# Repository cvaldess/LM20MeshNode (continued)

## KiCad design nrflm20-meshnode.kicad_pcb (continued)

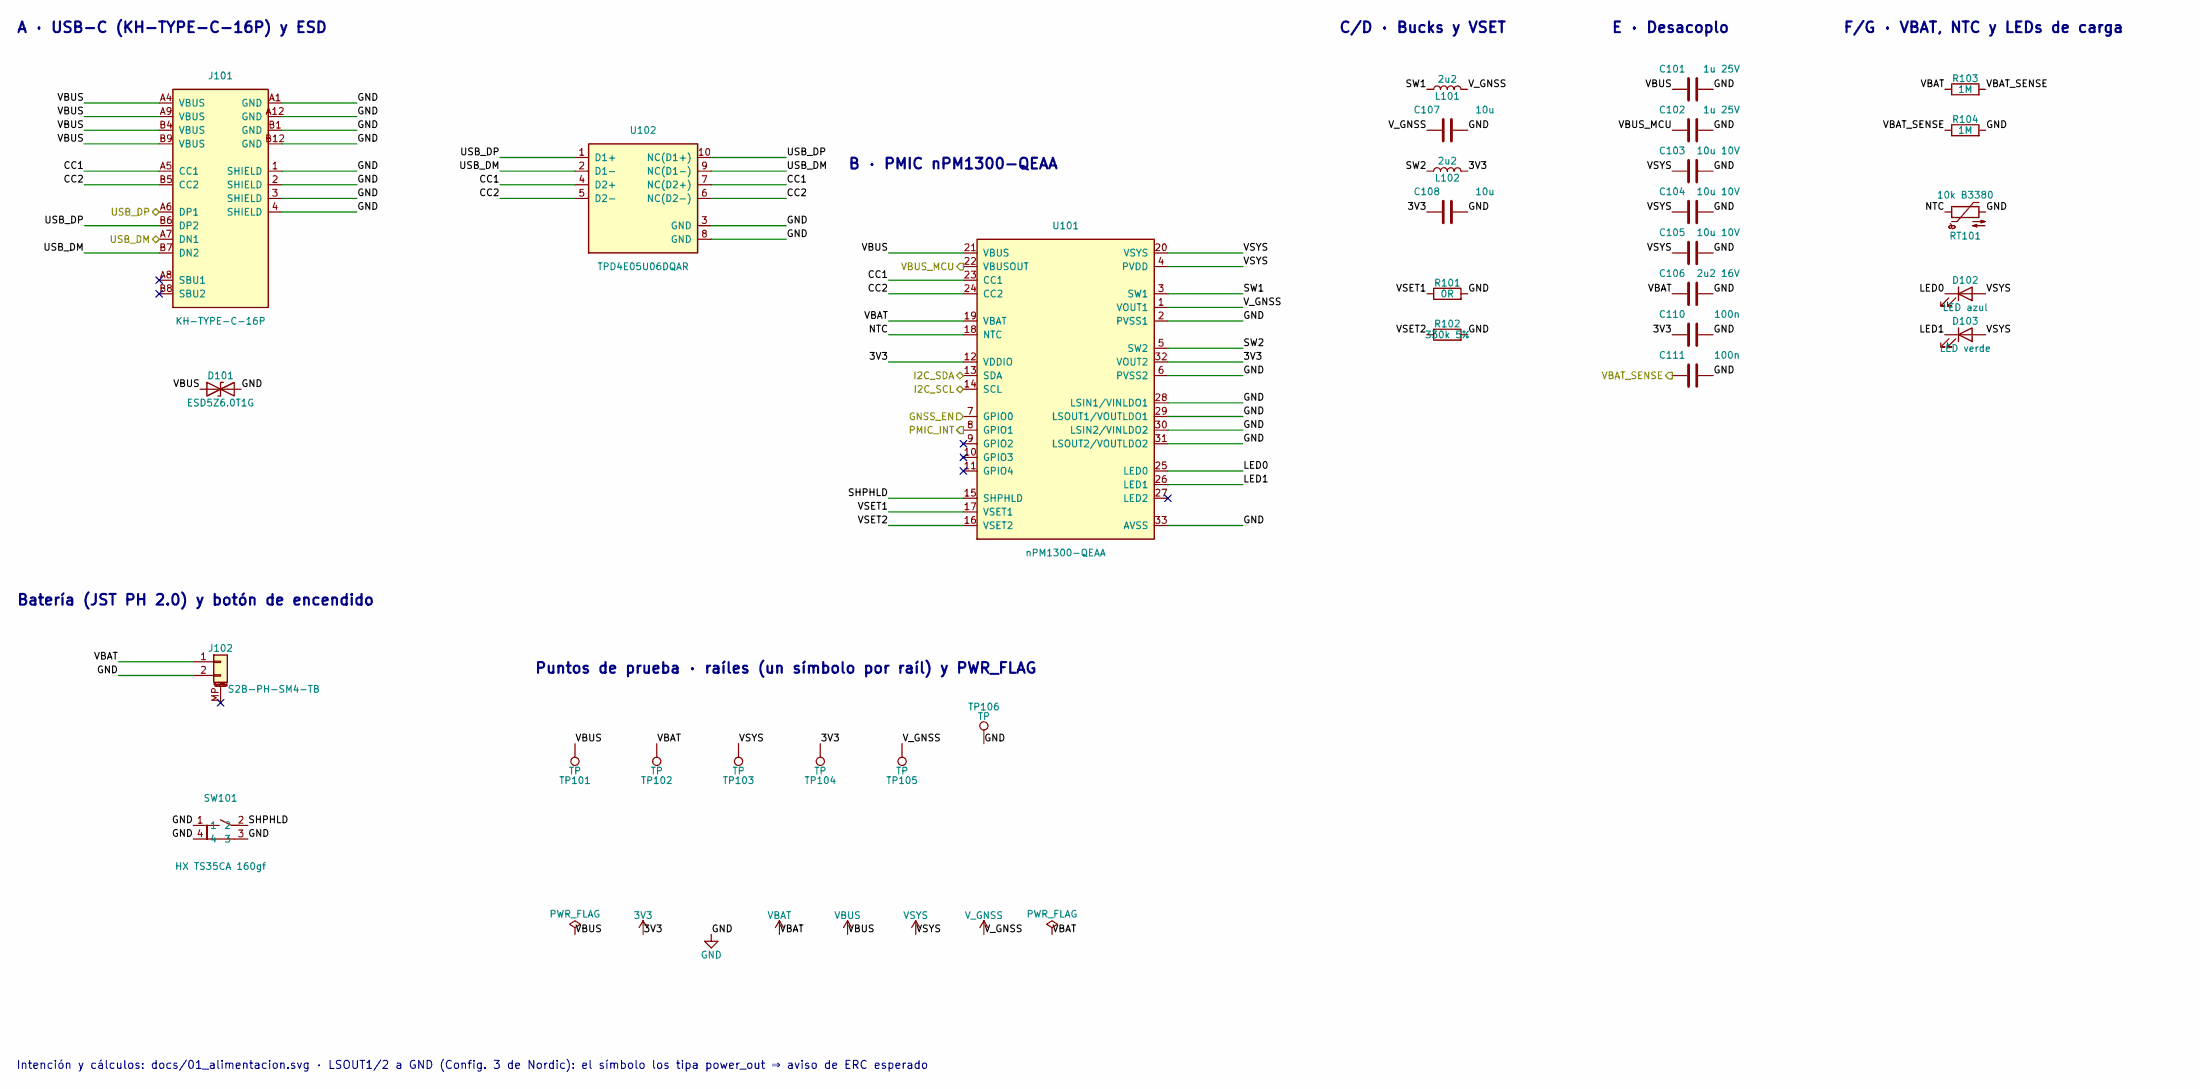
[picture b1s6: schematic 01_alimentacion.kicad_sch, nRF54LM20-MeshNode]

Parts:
C101, C102: 1u 25V; C_0402_1005Metric; MPN CL05A105KA5NQNC; LCSC Part C52923
C103, C104, C105: 10u 10V; C_0603_1608Metric
C106: 2u2 16V; C_0603_1608Metric; MPN CL10A225KO8NNNC; LCSC Part C23630
C107, C108: 10u; C_0603_1608Metric
C110, C111: 100n; C_0402_1005Metric; MPN CL05B104KO5NNNC; LCSC Part C1525
D101: ESD5Z6.0T1G; SOD-523F_L1.2-W0.8-LS1.7-RD; MPN ESD5Z6.0T1G; LCSC Part C82323
D102: LED azul; LED_0603_1608Metric; MPN XL-1608UBC-06A; LCSC Part C7371904
D103: LED verde; LED_0603_1608Metric; MPN XL-1608UGC-06A; LCSC Part C7371903
J101: KH-TYPE-C-16P; USB-C-SMD_KH-TYPE-C-16P; MPN KH-TYPE-C-16P; LCSC Part C709357
J102: S2B-PH-SM4-TB; JST_PH_S2B-PH-SM4-TB_1x02-1MP_P2.00mm_Horizontal; MPN S2B-PH-SM4-TB(LF)(SN); LCSC Part C295747
L101, L102: 2u2; L_Changjiang_FTC201610S; MPN APH201610C2R2MP01; LCSC Part C42455301
R101: 0R; R_0402_1005Metric; MPN RC0402FR-070RL; LCSC Part C106231
R102: 330k 5%; R_0402_1005Metric; MPN RC0402JR-07330KL; LCSC Part C137882
R103, R104: 1M; R_0402_1005Metric; MPN RC0402FR-071ML; LCSC Part C138033
RT101: 10k B3380; R_0402_1005Metric; MPN NCP15XH103F0SRC; LCSC Part C91636
SW101: HX TS35CA 160gf; KEY-SMD_HX-TS35CA-250GF; MPN HX TS35CA 160gf; LCSC Part C25168837
TP101, TP102, TP103, TP104, TP105, TP106: TP; TestPoint_Pad_D1.0mm
U101: nPM1300-QEAA; nPM1300-QFN32-EP3.5; MPN nPM1300-QEAA; LCSC Part C7501206
U102: TPD4E05U06DQAR; DFN2510-10_L2.5-W1.0-P0.50-BL; MPN TPD4E05U06DQAR; LCSC Part C22390021

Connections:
3V3: C108.1, C110.1, L102.2, TP104.1 (1_1), U101.12 (VDDIO), U101.32 (VOUT2); also elsewhere on the board
/01_alimentacion/CC1: J101.A5 (CC1), U101.23 (CC1), U102.4 (D2+), U102.7 (NC(D2+))
/01_alimentacion/CC2: J101.B5 (CC2), U101.24 (CC2), U102.5 (D2-), U102.6 (NC(D2-))
/01_alimentacion/LED0: D102.1 (K), U101.25 (LED0)
/01_alimentacion/LED1: D103.1 (K), U101.26 (LED1)
/01_alimentacion/NTC: RT101.1, U101.18 (NTC)
/01_alimentacion/SHPHLD: SW101.2, U101.15 (SHPHLD)
/01_alimentacion/SW1: L101.1, U101.3 (SW1)
/01_alimentacion/SW2: L102.1, U101.5 (SW2)
/01_alimentacion/VSET1: R101.1, U101.17 (VSET1)
/01_alimentacion/VSET2: R102.1, U101.16 (VSET2)
/GNSS_EN: U101.7 (GPIO0); also elsewhere on the board
/I2C_SCL: U101.14 (SCL); also elsewhere on the board
/I2C_SDA: U101.13 (SDA); also elsewhere on the board
/PMIC_INT: U101.8 (GPIO1); also elsewhere on the board
/USB_DM: J101.A7 (DN1), J101.B7 (DN2), U102.2 (D1-), U102.9 (NC(D1-)); also elsewhere on the board
/USB_DP: J101.A6 (DP1), J101.B6 (DP2), U102.1 (D1+), U102.10 (NC(D1+)); also elsewhere on the board
/VBAT_SENSE: C111.1, R103.2, R104.1; also elsewhere on the board
/VBUS_MCU: C102.1, U101.22 (VBUSOUT); also elsewhere on the board
GND: C101.2, C102.2, C103.2, C104.2, C105.2, C106.2, C107.2, C108.2, C110.2, C111.2, D101.2 (A2), J101.1 (SHIELD), J101.2 (SHIELD), J101.3 (SHIELD), J101.4 (SHIELD), J101.A1 (GND), J101.A12 (GND), J101.B1 (GND), J101.B12 (GND), J102.2, R101.2, R102.2, R104.2, RT101.2, SW101.1, SW101.3, SW101.4, TP106.1 (1_1), U101.2 (PVSS1), U101.6 (PVSS2), U101.28 (LSIN1/VINLDO1), U101.29 (LSOUT1/VOUTLDO1), U101.30 (LSIN2/VINLDO2), U101.31 (LSOUT2/VOUTLDO2), U101.33 (AVSS), U102.3 (GND), U102.8 (GND); also elsewhere on the board
VBAT: C106.1, J102.1, R103.1, TP102.1 (1_1), U101.19 (VBAT)
VBUS: C101.1, D101.1 (A1), J101.A4 (VBUS), J101.A9 (VBUS), J101.B4 (VBUS), J101.B9 (VBUS), TP101.1 (1_1), U101.21 (VBUS)
VSYS: C103.1, C104.1, C105.1, D102.2 (A), D103.2 (A), TP103.1 (1_1), U101.4 (PVDD), U101.20 (VSYS); also elsewhere on the board
V_GNSS: C107.1, L101.2, TP105.1 (1_1), U101.1 (VOUT1); also elsewhere on the board

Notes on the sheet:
B · PMIC nPM1300-QEAA
E · Desacoplo
F/G · VBAT, NTC y LEDs de carga
C/D · Bucks y VSET
Puntos de prueba · raíles (un símbolo por raíl) y PWR_FLAG
Batería (JST PH 2.0) y botón de encendido
A · USB-C (KH-TYPE-C-16P) y ESD
Intención y cálculos: docs/01_alimentacion.svg · LSOUT1/2 a GND (Config. 3 de Nordic): el símbolo los tipa power_out ⇒ aviso de ERC esperado

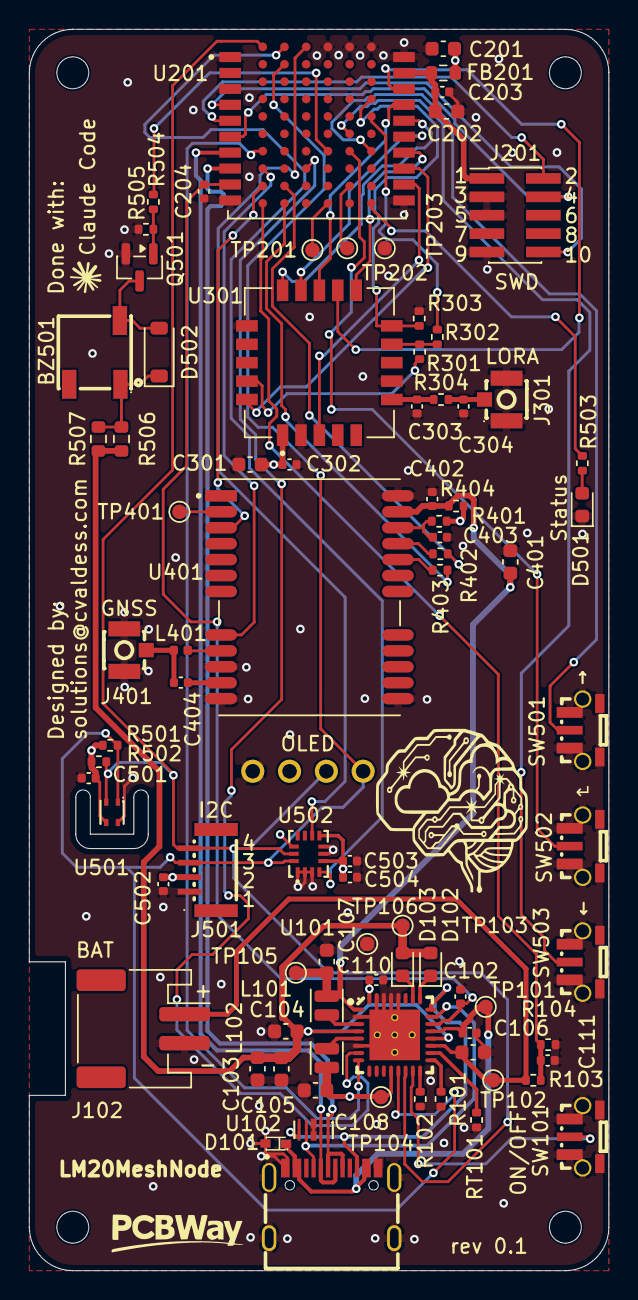
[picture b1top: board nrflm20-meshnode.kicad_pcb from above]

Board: 4 copper layers, 40.0 x 85.7 mm, 89 parts (1 on the bottom side), 65 nets.

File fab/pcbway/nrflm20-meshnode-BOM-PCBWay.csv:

"Designator","Qty","Manufacturer","Mfg Part #","Description/Value","Package/Footprint","LCSC Part #"
"BZ501","1","Huayu","HYG-5020A","HYG-5020A","easyeda2kicad:BUZ-SMD_3P-L5.0-W5.0-P3.50-BL","C7544810"
"C101,C102,C204,C502","4","Samsung","CL05A105KA5NQNC","1u 25V","Capacitor_SMD:C_0402_1005Metric","C52923"
"C103,C104,C105,C107,C108,C201,C202,C401","8","Generic","","10uF 20% 10V X7R 0603","Capacitor_SMD:C_0603_1608Metric",""
"C106","1","Samsung","CL10A225KO8NNNC","2u2 16V","Capacitor_SMD:C_0603_1608Metric","C23630"
"C110,C111,C203,C302,C402,C403,C501,C503,C504","9","Samsung","CL05B104KO5NNNC","100n","Capacitor_SMD:C_0402_1005Metric","C1525"
"C301","1","Generic","","22uF 20% 10V X7R 0603","Capacitor_SMD:C_0603_1608Metric",""
"C404","1","Samsung","CL05C560JB5NNNC","56p C0G","Capacitor_SMD:C_0402_1005Metric","C84707"
"D101","1","onsemi","ESD5Z6.0T1G","ESD5Z6.0T1G","easyeda2kicad:SOD-523F_L1.2-W0.8-LS1.7-RD","C82323"
"D102","1","XINGLIGHT","XL-1608UBC-06A","Blue LED","LED_SMD:LED_0603_1608Metric","C7371904"
"D103,D501","2","XINGLIGHT","XL-1608UGC-06A","Green LED","LED_SMD:LED_0603_1608Metric","C7371903"
"D502","1","JSMSEMI","1N4148W","1N4148W","Diode_SMD:D_SOD-123","C917030"
"DS501","1","HS","HS91L02W2C01","HS91L02W2C01","easyeda2kicad:OLED-TH_L38.0-W12.0_HS91L02W2C01","C5248081"
"FB201","1","Generic","","0R 0603 jumper","Resistor_SMD:R_0603_1608Metric",""
"J101","1","Kinghelm","KH-TYPE-C-16P","KH-TYPE-C-16P","easyeda2kicad:USB-C-SMD_KH-TYPE-C-16P","C709357"
"J102","1","JST","S2B-PH-SM4-TB(LF)(SN)","S2B-PH-SM4-TB","Connector_JST:JST_PH_S2B-PH-SM4-TB_1x02-1MP_P2.00mm_Horizontal","C295747"
"J201","1","HANXIA","HX PZ1.27-2x5P TP","SWD 2x5 1.27","Connector_PinHeader_1.27mm:PinHeader_2x05_P1.27mm_Vertical_SMD","C41376037"
"J301","1","BAT WIRELESS","BWU.FL-IPEX1","U.FL LoRa","easyeda2kicad:IPEX-SMD_BWIPX-1-001E","C5137195"
"J401","1","BAT WIRELESS","BWU.FL-IPEX1","U.FL GNSS","easyeda2kicad:IPEX-SMD_BWIPX-1-001E","C5137195"
"J501","1","BOOMELE","1.0T-4P","Qwiic 1.0T-4P","meshnode:BOOMELE_1.0T-4P_1x04-1MP_P1.00mm_Horizontal","C970137"
"L101,L102","2","APV","APH201610C2R2MP01","2u2","Inductor_SMD:L_Changjiang_FTC201610S","C42455301"
"L401","1","Murata","LQG15HS82NJ02D","82nH (active GNSS antenna bias)","Inductor_SMD:L_0402_1005Metric","C98002"
"Q501","1","HT (Jin Yu)","BSS138","BSS138","Package_TO_SOT_SMD:SOT-23","C27140738"
"R101,R301,R304","3","Yageo","RC0402FR-070RL","0R","Resistor_SMD:R_0402_1005Metric","C106231"
"R102","1","Yageo","RC0402JR-07330KL","330k 5%","Resistor_SMD:R_0402_1005Metric","C137882"
"R103,R104","2","Yageo","RC0402FR-071ML","1M","Resistor_SMD:R_0402_1005Metric","C138033"
"R303,R505","2","Yageo","RC0402FR-07100KL","100k","Resistor_SMD:R_0402_1005Metric","C60491"
"R401,R402,R403","3","UNI-ROYAL","0402WGF1001TCE","1k","Resistor_SMD:R_0402_1005Metric","C11702"
"R501,R502","2","Yageo","RC0402FR-074K7L","4k7","Resistor_SMD:R_0402_1005Metric","C105871"
"R503","1","UNI-ROYAL","0402WGF4700TCE","470R","Resistor_SMD:R_0402_1005Metric","C25117"
"R504","1","UNI-ROYAL","0402WGF2200TCE","220R","Resistor_SMD:R_0402_1005Metric","C25091"
"R506,R507","2","Generic","","10R 5% 0603","Resistor_SMD:R_0603_1608Metric",""
"RT101","1","Murata","NCP15XH103F0SRC","10k B3380","Resistor_SMD:R_0402_1005Metric","C91636"
"SW101,SW501,SW502,SW503","4","Hanxia","HX TS35CA 160gf","HX TS35CA 160gf","easyeda2kicad:KEY-SMD_HX-TS35CA-250GF","C25168837"
"U101","1","Nordic Semiconductor","nPM1300-QEAA","nPM1300-QEAA","meshnode:nPM1300-QFN32-EP3.5","C7501206"
"U102","1","DOWO","TPD4E05U06DQAR","TPD4E05U06DQAR","easyeda2kicad:DFN2510-10_L2.5-W1.0-P0.50-BL","C22390021"
"U201","1","Minew","ME54BS13 (nRF54LM20A)","ME54BS13","meshnode:ME54BS13",""
"U301","1","Ebyte","E22-900MM22S","E22-900MM22S","meshnode:E22-xxxMM22S",""
"U401","1","Ebyte","E108-GN04S","E108-GN04S","meshnode:E108-GN04S",""
"U501","1","Nyfea","SHT41-P-NF","SHT41-P-NF","easyeda2kicad:DFN-4_L1.5-W1.5-SHT41-AD1B-R2","C55108905"
"U502","1","STMicroelectronics","LSM6DS3TR-C","LSM6DS3TR-C","easyeda2kicad:LGA-14_L3.0-W2.5-P0.50-TL","C967633"

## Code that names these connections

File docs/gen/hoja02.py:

"""Hoja 02 · MCU — ME54BS13 (nRF54LM20A), desacoplo, SWD, UART de depuración (docs/02_mcu.svg). Referencias 2xx.
Fuentes: Minew ME54BS13 datasheet v1.0.0 (pinout p.6-9, §7 PCB), nRF54LM20A datasheet v1.0 (clock pins p.1240,
SERIALxx por puerto, GPIOTE por puerto). El mapa de pines MAPA es la fuente para la captura y para la variante."""
import os

from svgkit import *  # noqa: F401,F403
from me54bs13_pads import pinmap as PADS  # pad -> nombre de puerto

OUT = os.path.normpath(os.path.join(os.path.dirname(os.path.abspath(__file__)), "..", "02_mcu.svg"))

# señal -> (puerto, tipo de etiqueta, periférico / nota)
MAPA = {
    "LORA_SCK": ("P1.17", "sig", "SPIM22 SCK (clock pin) · castellado 16"),
    "LORA_MOSI": ("P1.16", "sig", "SPIM22 MOSI · castellado 17"),
    "LORA_MISO": ("P1.15", "sig", "SPIM22 MISO · castellado 18"),
    "LORA_NSS": ("P1.18", "sig", "GPIO · castellado 15"),
    "LORA_BUSY": ("P1.19", "sig", "GPIO entrada · castellado 14"),
    "LORA_DIO1": ("P1.23", "sig", "GPIOTE20 (IRQ) · castellado 13"),
    "LORA_NRST": ("P1.26", "sig", "GPIO · castellado 12"),
    "LORA_RXEN": ("P1.13", "sig", "GPIO (RadioLib RXEN)"),
    "LORA_TXEN": ("P1.12", "sig", "GPIO opcional (R302 DNP)"),
    "I2C_SDA": ("P0.03", "sig", "TWIM30 SDA (como la DK)"),
    "I2C_SCL": ("P0.04", "sig", "TWIM30 SCL (clock pin)"),
    "IMU_INT1": ("P0.02", "sig", "GPIOTE30 ← INT1 del LSM6DS3TR-C"),
    "IMU_INT2": ("P0.05", "sig", "GPIOTE30 ← INT2 del LSM6DS3TR-C"),
    "GNSS_TX": ("P1.03", "sig", "UARTE20 TXD → RXD del GNSS"),
    "GNSS_RX": ("P1.29", "sig", "UARTE20 RXD ← TXD del GNSS"),
    "GNSS_PPS": ("P1.04", "sig", "GPIOTE20 (PIN_GPS_PPS)"),
    "GNSS_RST": ("P1.00", "sig", "salida en drenador abierto"),
    "GNSS_EN": ("P1.05", "sig", "→ GPIO0 del nPM1300 (PIN_GPS_EN)"),
    "PMIC_INT": ("P1.06", "sig", "GPIOTE20 ← GPIO1 del nPM1300"),
    "VBAT_SENSE": ("P1.30", "sig", "AIN2 (BATTERY_PIN)"),
    "BTN_UP": ("P1.27", "sig", "GPIOTE20, pull-up interno"),
    "BTN_OK": ("P1.28", "sig", "GPIOTE20, pull-up interno (BUTTON1)"),
    "BTN_DOWN": ("P1.25", "sig", "GPIOTE20, pull-up interno"),
    "BUZZER": ("P1.09", "sig", "PWM20 (PIN_BUZZER)"),
    "LED_STAT": ("P2.00", "sig", "GPIO salida (PIN_LED1)"),
    "DBG_TX": ("P2.02", "loc", "UARTE00 TXD (pin dedicado) → TP201"),
    "DBG_RX": ("P2.07", "loc", "UARTE00 RXD (pin dedicado) ← TP202"),
}
PORT2PAD = {v: k for k, v in PADS.items() if v.startswith("P")}
NET_OF_PORT = {p: (n, k) for n, (p, k, _) in MAPA.items()}


def dibujar():
    W, H = 1720, 1340
    nueva(W, H, "02 · MCU — ME54BS13 (nRF54LM20A)",
          "nrf54lm20-meshnode · hoja 2 · referencias 2xx · intención de 02_mcu.kicad_sch · mapa de pines elegido por mí (revisar con las huellas en el PCB)")
    leyenda(760, 40)

    # ---------------------------------------------------------------- A · módulo
    frame(20, 76, 800, 1250, "A · U201 ME54BS13 — nRF54LM20A, antena PCB, cristales y DCDC internos")
    from simbolos_lib import me54bs13  # misma disposición que el símbolo de libs/meshnode.kicad_sym
    pins = me54bs13()
    left = sorted([p for p in pins if p["angle"] == 0], key=lambda p: -p["y"])
    right = sorted([p for p in pins if p["angle"] == 180], key=lambda p: -p["y"])
    top = max(p["y"] for p in pins if p["angle"] in (0, 180))

    def rows(side):
        out, prev = [], None
        for p in side:
            if prev is not None:
                out += [None] * (round((prev - p["y"]) / 2.54) - 1)
            out.append((p["number"], p["name"])); prev = p["y"]
        return out
    lr, rr = rows(left), rows(right)
    lr = [None] * round((top - left[0]["y"]) / 2.54) + lr
    e, h = ic2(300, 140, 250, "U201", "ME54BS13 · Minew", lr, rr, pitch=18.5, stub=22)
    spec = {}
    for p in pins:
        num, nm = p["number"], p["name"]
        port = nm.split("/")[0]
        if p["angle"] == 90:
            continue
        if port in NET_OF_PORT:
            spec[num] = NET_OF_PORT[port]
        elif nm.startswith("P"):
            spec[num] = ("", "nc")
    spec.update({"19": ("VCC_MCU", "loc"), "9": ("VBUS_MCU", "sig"), "8": ("USB_DP", "sig"), "7": ("USB_DM", "sig"),
                 "4": ("SWD_RST", "loc"), "5": ("SWDIO", "loc"), "6": ("SWDCLK", "loc"), "2": ("", "nc")})
    pin_labels(e, spec)
    gy = 140 + h + 10
    gnds = [p["number"] for p in pins if p["angle"] == 90]
    T(425, gy + 8, "GND: " + " · ".join(gnds) + "  (todas, con vía cada una)", "td", "middle")
    gnd(425, gy + 16)
    notes(40, gy + 56, [
        "Castellado 2 (RF) sin conectar: antena PCB del módulo (configuración por defecto).",
        "P1.01/P1.02 = NFC por defecto · P1.20/P1.21 = cristal de 32 kHz interno (no salen).",
        "Los GPIO libres quedan sin conectar (NC): el pad del módulo se suelda igual."])

    # ---------------------------------------------------------------- B · alimentación del módulo
    frame(840, 76, 860, 250, "B · Alimentación del módulo (Minew §7.3: π reservada junto a VCC)")
    label(890, 140, "3V3", "pwr", "end"); P([(890, 140), (980, 140)], "pw"); dot(940, 140)
    cap_v(940, 140, "C201", "10 µF", 44, "l"); gnd(940, 184)
    res_h(980, 140, "FB201", "0 Ω (o ferrita 600 Ω)", 90, sym="symp")
    P([(1070, 140), (1220, 140)], "pw"); dot(1110, 140); dot(1170, 140)
    cap_v(1110, 140, "C202", "10 µF", 44); gnd(1110, 184)
    cap_v(1170, 140, "C203", "100 nF", 44); gnd(1170, 184)
    label(1220, 140, "VCC_MCU", "loc")
    notes(860, 240, ["FB201 = π de Minew: 0 Ω de serie; ferrita (CBW160808U601T, cajón) si el",
                     "buck mete ruido en el BLE. C202/C203 a ≤ 0,5 mm de la pata 19, 2 vías a GND."])
    caps_to_gnd(1430, 140, "VBUS_MCU", "sig", [("C204", "1 µF 25 V")])
    notes(1350, 240, ["VBUS del módulo (pata 9): alimenta", "el regulador del PHY USB interno."])

    # ---------------------------------------------------------------- C · SWD
    frame(840, 340, 430, 270, "C · SWD — cabecera Cortex 2×5 1,27 mm")
    ej, _ = ic2(990, 400, 100, "J201", "2×5 1,27 SMD", [("1", "VTref"), ("3", "GND"), ("5", "GND"), ("7", "KEY"), ("9", "GNDdet")],
                [("2", "SWDIO"), ("4", "SWCLK"), ("6", "SWO"), ("8", "NC"), ("10", "nRESET")], pitch=24, stub=20)
    pin_labels(ej, {"1": ("VCC_MCU", "loc"), "3": ("", "gnd"), "5": ("", "gnd"), "7": ("", "nc"), "9": ("", "gnd"),
                    "2": ("SWDIO", "loc"), "4": ("SWDCLK", "loc"), "6": ("", "nc"), "8": ("", "nc"),
                    "10": ("SWD_RST", "loc")})
    notes(856, 560, ["Sólo para grabar el bootloader la primera vez (luego UF2/DFU por USB).",
                     "SWO sin conectar: P2.07 se usa como RXD de depuración."])

    # ---------------------------------------------------------------- D · UART de depuración
    frame(1290, 340, 410, 270, "D · UART de depuración (UARTE00)")
    tp(1340, 410, "TP201"); label(1390, 410, "DBG_TX", "loc")
    tp(1340, 450, "TP202"); label(1390, 450, "DBG_RX", "loc")
    tp(1340, 490, "TP203"); label(1390, 490, "GND", "pwr")
    notes(1306, 536, ["Pines dedicados de UARTE00: TXD P2.02 y RXD P2.07.",
                      "Por si el USB nativo no arranca (consola del core).",
                      "Huella TestPoint:TestPoint_Pad_D1.0mm (todos los TP)."], dy=19)

    # ---------------------------------------------------------------- E · mapa de pines
    frame(840, 624, 860, 702, "E · Mapa de pines (base de la variante de Meshtastic)")
    rows_ = []
    for sig, (port, kind, note) in MAPA.items():
        pad = PORT2PAD[port]
        rows_.append((sig, port, pad, note))
    tabla(840, 664, 860, [860, 990, 1060, 1110], ["Señal", "Puerto", "Pad", "Periférico / nota"], rows_, dy=20,
          mono=(0, 1, 2))
    notes(856, 1262, [
        "Reglas del nRF54LM20A: SERIAL2x sólo en P1/P3, SERIAL30 en P0, SERIAL00 en P2; IRQ y SENSE sólo en P0/P1/P3;",
        "SCK/SCL en clock pins. LoRa: SPIM22 (como la DK) · GNSS: UARTE20 · I²C: TWIM30 · depuración: UARTE00.",
        ("E22 con cristal pasivo ⇒ la variante NO define SX126X_DIO3_TCXO_VOLTAGE.", "tw")], dy=18)
    guardar(OUT)


if __name__ == "__main__":
    dibujar()

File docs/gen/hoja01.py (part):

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    diode_v(xr + 70, y1, "D101", "ESD5Z6.0", 44, "r", "tvs"); gnd(xr + 70, y1 + 44)
    label(xr + 130, y1, "VBUS", "pwr")
    label(e["A5"][0], e["A5"][1], "CC1", "loc"); label(e["B5"][0], e["B5"][1], "CC2", "loc")
    label(e["A6/B6"][0], e["A6/B6"][1], "USB_DP", "sig"); label(e["A7/B7"][0], e["A7/B7"][1], "USB_DM", "sig")
    nc(*e["A8"]); nc(*e["B8"])
    for k in ("A1/B12", "A12/B1", "SH1-4"):
        x, y = e[k]; P([(x, y), (x + 14, y)]); gnd(x + 14, y)
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    e2, h2 = ic2(410, 226, 100, "U102", "TPD4E05U06DQAR · DOWO", [("1", "D1+"), ("2", "D1-"), ("4", "D2+"), ("5", "D2-")],
                 [("10", "NC·D1+"), ("9", "NC·D1-"), ("7", "NC·D2+"), ("6", "NC·D2-"), None, ("3", "GND"),
                  ("8", "GND")], pitch=22, top_pad=16, stub=18)
    for a, b, n, kind in (("1", "10", "USB_DP", "sig"), ("2", "9", "USB_DM", "sig"), ("4", "7", "CC1", "loc"),
                          ("5", "6", "CC2", "loc")):
        label(e2[a][0], e2[a][1], n, kind, "end"); label(e2[b][0], e2[b][1], n, kind)
    for k in ("3", "8"):
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    # ---------------------------------------------------------------- B · nPM1300
    frame(640, 76, 600, 720, "B · PMIC nPM1300-QEAA (QFN32, EP = AVSS)")
    L = [("21", "VBUS"), ("22", "VBUSOUT"), ("23", "CC1"), ("24", "CC2"), None, ("19", "VBAT"), ("18", "NTC"), None,
         ("12", "VDDIO"), ("13", "SDA"), ("14", "SCL"), None, ("7", "GPIO0"), ("8", "GPIO1"), ("9", "GPIO2"),
         ("10", "GPIO3"), ("11", "GPIO4"), None, ("15", "SHPHLD"), ("17", "VSET1"), ("16", "VSET2")]
    R = [("20", "VSYS"), ("4", "PVDD"), None, ("3", "SW1"), ("1", "VOUT1"), ("2", "PVSS1"), None, ("5", "SW2"),
         ("32", "VOUT2"), ("6", "PVSS2"), None, ("28", "LSIN1/VINLDO1"), ("29", "LSOUT1/VOUTLDO1"),
         ("30", "LSIN2/VINLDO2"), ("31", "LSOUT2/VOUTLDO2"), None, ("25", "LED0"), ("26", "LED1"), ("27", "LED2"),
         None, ("33", "AVSS (EP)")]
    eb, hb = ic2(850, 140, 190, "U101", "nPM1300-QEAA · C7501206", L, R, pitch=26)
    pin_labels(eb, {"21": ("VBUS", "pwr"), "22": ("VBUS_MCU", "sig"), "23": ("CC1", "loc"), "24": ("CC2", "loc"),
                    "19": ("VBAT", "pwr"), "18": ("NTC", "loc"), "12": ("3V3", "pwr"), "13": ("I2C_SDA", "sig"),
                    "14": ("I2C_SCL", "sig"), "7": ("GNSS_EN", "sig"), "8": ("PMIC_INT", "sig"), "9": ("", "nc"),
                    "10": ("", "nc"), "11": ("", "nc"), "15": ("SHPHLD", "loc"), "17": ("VSET1", "loc"),
                    "16": ("VSET2", "loc"), "20": ("VSYS", "pwr"), "4": ("VSYS", "pwr"), "3": ("SW1", "loc"),
                    "1": ("V_GNSS", "pwr"), "2": ("", "gnd"), "5": ("SW2", "loc"), "32": ("3V3", "pwr"),
                    "6": ("", "gnd"), "28": ("", "gnd"), "29": ("", "gnd"), "30": ("", "gnd"), "31": ("", "gnd"),
                    "25": ("LED0", "loc"), "26": ("LED1", "loc"), "27": ("", "nc"), "33": ("", "gnd")})
    notes(656, 140 + hb + 22, [
        "GPIO0 ← MCU: el firmware la asigna a BUCKENCTRL (enciende BUCK1 = GNSS) ⇒ PIN_GPS_EN.",
        "GPIO1 → MCU: interrupción (VBUS, carga, botón). GPIO2-4 libres (pull-down interno de serie).",
        "LSIN/LSOUT 1-2 sin uso ⇒ a GND, como la «Configuration 3» de Nordic (PS v1.3 §9.3.3).",
        "PVSS1/2 a GND con vía junto al pad · EP con 5 vías térmicas (huella nPM1300-QFN32-EP3.5)."])

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    frame(1260, 76, 440, 300, "C · Bucks (L 2,2 µH APH201610C2R2MP01, 0806)")
    for yy, sw, ref, cref, net, txt in (
            (140, "SW1", "L101", "C107", "V_GNSS", ["BUCK1 = raíl del GNSS: APAGADO al arrancar (VSET1 a GND).",
                                                    "El firmware lo pone a 3,3 V y lo enciende con GPIO0."]),
            (270, "SW2", "L102", "C108", "3V3", ["BUCK2 = 3V3 principal desde el arranque (VSET2 330 kΩ).",
                                                 "Pico: E22 140 + MCU ~15 + OLED ~20 = 175 de 200 mA."])):
        label(1300, yy, sw, "loc", "end"); ind_h(1300, yy, ref, "2,2 µH", 90); P([(1390, yy), (1470, yy)], "pw")
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
    # ---------------------------------------------------------------- D · VSET
    frame(1260, 390, 440, 180, "D · Tensión de arranque de los bucks (tablas 17/18)")
    label(1330, 440, "VSET1", "loc", "end"); P([(1330, 440), (1350, 440)]); res_v(1350, 440, "R101", "0 Ω", 50)
    gnd(1350, 490)
    label(1510, 440, "VSET2", "loc", "end"); P([(1510, 440), (1530, 440)])
    res_v(1530, 440, "R102", "330 kΩ 5 %", 50); gnd(1530, 490)
    notes(1280, 530, ["R101 0 Ω ⇒ BUCK1 apagado (con 330 kΩ arrancaría a 2,7 V).",
                      "R102 250–500 kΩ ⇒ 3,3 V: 330 kΩ 5 % (313–347 kΩ) basta. Comprar."])

    # ---------------------------------------------------------------- G · botón y LEDs
    frame(1260, 584, 440, 330, "G · Botón de encendido y LEDs de carga")
    label(1310, 640, "SHPHLD", "loc", "end"); P([(1310, 640), (1330, 640)]); sw_v(1330, 640, "SW101", "PWR · HX TS35CA", 56)
    gnd(1330, 696)
    notes(1280, 740, ["Pata 2 = SHPHLD; 1, 3, 4 a GND.", "Sale del ship mode;", "larga = reset duro."])
    for yy, ref, val, net in ((630, "D102", "azul · ERROR", "LED0"), (740, "D103", "verde · CARGA", "LED1")):
        label(1570, yy, "VSYS", "pwr", "end"); P([(1570, yy), (1590, yy)])
        led_v(1590, yy, ref, val, 44); P([(1590, yy + 44), (1590, yy + 56)]); label(1590, yy + 65, net, "loc", "middle")
    notes(1280, 846, ["LEDDRV = sumidero de 5 mA: sin resistencia (como la referencia).",
                      "Por defecto LED0 = error del cargador, LED1 = cargando. LED2 sin uso.",
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                      "comprobarla antes de enchufar (pata 1 = +).",
                      "El pack debe llevar su protección (PCM): el nPM1300",
                      "no corta por sobredescarga ni sobrecorriente."])
    label(1090, 990, "NTC", "loc", "end"); P([(1090, 990), (1110, 990)]); res_v(1110, 990, "RT101", "NTC 10k B3380", 50)
    gnd(1110, 1040)
    notes(1040, 1088, ["NCP15XH103F0SRC (cajón): 10 kΩ ±1 %,", "B25/50 3380 K = tabla 11 del nPM1300.",
                       "Junto al conector de batería (el pack", "no trae NTC)."])
    label(1400, 990, "VBAT", "pwr", "end"); P([(1400, 990), (1420, 990)]); res_v(1420, 990, "R103", "1 MΩ", 46)
    dot(1420, 1036); P([(1420, 1036), (1440, 1036)]); label(1440, 1036, "VBAT_SENSE", "sig")
    res_v(1420, 1036, "R104", "1 MΩ", 46, side="l"); gnd(1420, 1082)
    P([(1540, 1036), (1600, 1036)]); dot(1600, 1036)
    cap_v(1600, 1036, "C111", "100 nF", 40); gnd(1600, 1076)
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        "Tras un reset: cargador APAGADO, VTERM 3,60 V, ICHG 32 mA, VBUS 100 mA, BUCK1 apagado.",
        "1. VBUSINILIM0 = 500 mA tras leer CC (USBCDETECTSTATUS) + TASK.UPDATE.ILIMSW.",
        "2. ADCNTCRSEL = 10 k · BCHGVTERM = 4,20 V · BCHGISET = 0,5 C · BCHGENABLESET = 1.",
        "3. BUCK1NORMVOUT = 3,3 V + BUCKSWCTRLSEL · BUCKENCTRL: GPIO0 → BUCK1.",
        "4. GPIOMODE1 = salida de IRQ (→ PMIC_INT): VBUS, carga y SHPHLD.",
        "5. Batería: ADC del nPM1300 por I²C, o VBAT_SENSE con BATTERY_PIN.",
        ("🚨 Sin driver: LoRa y BLE van (3V3 arranca solo); NO carga y el GNSS no enciende.", "tw"),
        ("🚨 Sólo USB, sin batería: 100 mA de VBUS no dan para TX LoRa hasta subir el límite.", "tw"),
    ], dy=19)
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
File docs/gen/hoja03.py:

"""Hoja 03 · LoRa — E22-900MM22S (SX1262, 22 dBm, cristal pasivo) y U.FL (docs/03_lora.svg). Referencias 3xx.
Fuente: Ebyte E22-M user manual §3.1 (pinout), §4.1-4.2 (TXEN/RXEN, tabla 1), §5.1 (circuito recomendado)."""
import os

from svgkit import *  # noqa: F401,F403

OUT = os.path.normpath(os.path.join(os.path.dirname(os.path.abspath(__file__)), "..", "03_lora.svg"))


def dibujar():
    W, H = 1720, 1000
    nueva(W, H, "03 · LoRa — E22-900MM22S (SX1262, 22 dBm)",
          "nrf54lm20-meshnode · hoja 3 · referencias 3xx · intención de 03_lora.kicad_sch")
    leyenda(760, 40)

    frame(20, 76, 860, 600, "A · U301 E22-900MM22S")
    L = [("1", "VCC"), None, ("3", "NRST"), None, ("14", "NSS"), ("15", "SCK"), ("13", "MOSI"), ("12", "MISO"), None,
         ("2", "GND"), ("7", "GND"), ("16", "GND")]
    R = [("6", "ANT"), None, ("9", "TXEN"), ("10", "RXEN"), None, ("11", "BUSY"), ("20", "DIO1"), ("19", "DIO2"),
         ("18", "DIO3"), None, ("4", "NC"), ("5", "NC"), ("8", "NC"), ("17", "NC")]
    e, h = ic2(320, 150, 170, "U301", "E22-900MM22S · Ebyte", L, R, pitch=28)
    pin_labels(e, {"1": ("3V3", "pwr"), "3": ("LORA_NRST", "sig"), "14": ("LORA_NSS", "sig"),
                   "15": ("LORA_SCK", "sig"), "13": ("LORA_MOSI", "sig"), "12": ("LORA_MISO", "sig"),
                   "2": ("", "gnd"), "7": ("", "gnd"), "16": ("", "gnd"), "6": ("LORA_ANT", "loc"),
                   "9": ("TXEN", "loc"), "10": ("LORA_RXEN", "sig"), "11": ("LORA_BUSY", "sig"),
                   "20": ("LORA_DIO1", "sig"), "19": ("DIO2", "loc"), "18": ("", "nc"), "4": ("", "nc"),
                   "5": ("", "nc"), "8": ("", "nc"), "17": ("", "nc")})
    notes(40, 150 + h + 40, [
        "Interruptor de RF interno (tabla 1): TXEN=1/RXEN=0 ⇒ TX · TXEN=0/RXEN=1 ⇒ RX · 0/0 ⇒ apagado.",
        "DIO2 gobierna TXEN (SX126X_DIO2_AS_RF_SWITCH) y RadioLib mueve RXEN (SX126X_RXEN = P1.13).",
        "DIO3 sin conectar: el MM22S lleva cristal PASIVO (la versión «(T)» lleva TCXO y tiene la misma huella).",
        ("⇒ la variante NO define SX126X_DIO3_TCXO_VOLTAGE (la DK sí, con el E22-900M30S).", "tw"),
        "NRST con pull-up interno del SX1262: lo mueve el MCU (LORA_NRST)."], dy=19)

    # ---------------------------------------------------------------- B · TXEN / RXEN
    frame(900, 76, 800, 300, "B · Control del interruptor de antena")
    label(980, 140, "DIO2", "loc", "end"); res_h(980, 140, "R301", "0 Ω", 80); P([(1060, 140), (1150, 140)])
    dot(1150, 140); label(1170, 140, "TXEN", "loc"); P([(1150, 140), (1170, 140)])
    label(980, 200, "LORA_TXEN", "sig", "end"); res_h(980, 200, "R302", "0 Ω DNP", 80, sym="dnp")
    P([(1060, 200), (1150, 200), (1150, 140)])
    label(1330, 140, "LORA_RXEN", "sig", "end"); P([(1330, 140), (1360, 140)]); dot(1360, 140)
    res_v(1360, 140, "R303", "100 kΩ", 50); gnd(1360, 190)
    notes(920, 260, ["R301 montada: TXEN = DIO2 (lo que hace Meshtastic). R302 sin montar: alternativa con",
                     "TXEN desde el MCU (P1.12) si hiciera falta. R303: RXEN a 0 mientras el MCU arranca",
                     "(los GPIO salen en alta impedancia) ⇒ interruptor apagado, sin estado indefinido."])

    # ---------------------------------------------------------------- C · antena
    frame(900, 390, 800, 246, "C · Antena 868 MHz: π de adaptación + U.FL")
    label(960, 450, "LORA_ANT", "loc", "end"); P([(960, 450), (990, 450)], "rf")
    dot(990, 450); cap_v(990, 450, "C303", "DNP", 44, "l", pc="plated"); gnd(990, 494)
    res_h(990, 450, "R304", "0 Ω", 90, cls="rf")
    dot(1080, 450); cap_v(1080, 450, "C304", "DNP", 44, pc="plated"); gnd(1080, 494)
    P([(1080, 450), (1200, 450)], "rf")
    ej, _ = ic2(1220, 430, 110, "J301", "BWU.FL-IPEX1 · C5137195", [("1", "SIG")], [("2", "GND"), ("3", "GND")], pitch=24)
    P([(1200, 450), ej["1"]], "rf")
    for k in ("2", "3"):
        x, y = ej[k]; P([(x, y), (x + 10, y)]); gnd(x + 10, y)
    notes(920, 540, ["Pista de 50 Ω en coplanar con plano de GND (4 capas) desde la pata 6 hasta el U.FL;",
                     "π en 0402 pegada al módulo: 0 Ω de serie y los shunts sin montar salvo que haya que",
                     "adaptar midiendo. Vías de GND a lo largo de la pista. Lejos del U.FL del GNSS."])

    # ---------------------------------------------------------------- D · desacoplo
    frame(20, 690, 860, 150, "D · Desacoplo (E22 §5.1: «external ceramic filter capacitor recommended»)")
    caps_to_gnd(120, 745, "3V3", "pwr", [("C301", "22 µF 10 V"), ("C302", "100 nF")], dx=90)
    notes(340, 747, ["C301 cubre los picos de TX (140 mA a 22 dBm) sin tirar del buck;",
                     "C302 pegado a la pata 1. 3V3 llega del BUCK2 (hoja 01)."])

    rows = [("U301", "módulo LoRa SX1262", "Ebyte E22-900MM22S", "SMD 10×10", "—", "cajón #195 (2)"),
            ("J301", "conector antena", "BAT WIRELESS BWU.FL-IPEX1", "SMD", "C5137195", "cajón #210"),
            ("R301 R304", "0 Ω", "Yageo RC0402FR-070RL", "0402", "C106231", "cajón #10"),
            ("R302", "0 Ω (DNP)", "—", "0402", "—", "—"),
            ("R303", "100 kΩ 1 %", "Yageo RC0402FR-07100KL", "0402", "C60491", "cajón #11"),
            ("C301", "22 µF 10 V X7R", "—", "0603", "—", "cajón #146"),
            ("C302", "100 nF 16 V X7R", "Samsung CL05B104KO5NNNC", "0402", "C1525", "cajón #22"),
            ("C303 C304", "shunt π (DNP)", "C0G según medida", "0402", "—", "—")]
    frame(900, 650, 800, 300, "Piezas de la hoja")
    tabla(900, 690, 800, [920, 1010, 1150, 1350, 1440, 1530], ["Ref.", "Qué es", "Pieza", "Encaps.", "LCSC", "Stock"],
          rows, dy=24, mono=(0, 4))
    frame(20, 854, 860, 126, "Notas de colocación")
    notes(36, 894, ["• E22 a la derecha del ME54BS13: su SPI sale de los castellados 12-18 y va en superficie.",
                    "• Antena LoRa y antena BLE del módulo en cantos distintos; plano de GND sin cortes bajo el E22.",
                    "• Nada de pistas bajo el E22 salvo GND (manual §4.1)."], dy=20)
    guardar(OUT)


if __name__ == "__main__":
    dibujar()

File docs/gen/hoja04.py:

"""Hoja 04 · GNSS — E108-GN04S y U.FL para antena activa o pasiva (docs/04_gnss.svg). Referencias 4xx.
Fuentes: Ebyte E108-GN04 user manual V1.3 §3.2 (pinout), §4.2 (circuito), §2.3 (consumo 25-27 mA, sin sleep);
«Recommended wiring diagram of GNSS module antenna» V1.0 (82 nH desde VCC_RF, 56 pF en serie)."""
import os

from svgkit import *  # noqa: F401,F403

OUT = os.path.normpath(os.path.join(os.path.dirname(os.path.abspath(__file__)), "..", "04_gnss.svg"))


def dibujar():
    W, H = 1720, 1000
    nueva(W, H, "04 · GNSS — E108-GN04S (BDS/GPS/GLONASS/Galileo)",
          "nrf54lm20-meshnode · hoja 4 · referencias 4xx · intención de 04_gnss.kicad_sch")
    leyenda(760, 40)

    frame(20, 76, 860, 610, "A · U401 E108-GN04S")
    L = [("23", "VCC"), ("22", "V_BCKP"), None, ("21", "RXD"), ("20", "TXD"), None, ("8", "RESET_N"),
         ("2", "SAFEBOOT_N"), ("4", "EXTINT"), ("3", "1PPS"), None, ("10", "GND"), ("12", "GND"), ("13", "GND"),
         ("24", "GND")]
    R = [("11", "RF_IN"), ("9", "VCC_RF"), ("14", "LNA_EN"), None] + [(n, "NC") for n in
                                                                      ("1", "5", "6", "7", "15", "16", "17", "18", "19")]
    e, h = ic2(360, 150, 180, "U401", "E108-GN04S · Ebyte", L, R, pitch=26)
    pin_labels(e, {"23": ("V_GNSS", "pwr"), "22": ("V_BCKP", "loc"), "21": ("GNSS_RXD", "loc"),
                   "20": ("GNSS_TXD", "loc"), "8": ("GNSS_RST", "sig"), "2": ("SAFEBOOT", "loc"), "4": ("", "nc"),
                   "3": ("GNSS_PPS", "sig"), "10": ("", "gnd"), "12": ("", "gnd"), "13": ("", "gnd"),
                   "24": ("", "gnd"), "11": ("GNSS_RFIN", "loc"), "9": ("VCC_RF", "loc"), "14": ("", "nc"),
                   **{n: ("", "nc") for n in ("1", "5", "6", "7", "15", "16", "17", "18", "19")}})
    notes(40, 150 + h + 36, [
        "Consumo 25–27 mA (§2.3) y SIN modo sleep documentado ⇒ se le corta VCC: V_GNSS = BUCK1 del nPM1300.",
        "V_BCKP desde 3V3 (siempre vivo): mantiene RTC y efemérides con VCC cortado ⇒ arranque en caliente (~1 s).",
        "RESET_N: pull-up interno, «dejar al aire si no se usa» ⇒ el MCU sólo lo baja (drenador abierto).",
        "EXTINT y LNA_EN sin uso (al aire, §3.2). SAFEBOOT_N a un punto de prueba (recuperación de firmware).",
        "UART 38400 baudios por defecto, NMEA 4.11 / UBX."], dy=19)

    # ---------------------------------------------------------------- B · UART y backup
    frame(900, 76, 800, 330, "B · UART, backup y puntos de prueba")
    label(990, 140, "GNSS_TX", "sig", "end"); res_h(990, 140, "R402", "1 kΩ", 80); label(1070, 140, "GNSS_RXD", "loc")
    label(990, 190, "GNSS_RX", "sig", "end"); res_h(990, 190, "R403", "1 kΩ", 80); label(1070, 190, "GNSS_TXD", "loc")
    label(1330, 140, "3V3", "pwr", "end"); res_h(1330, 140, "R401", "1 kΩ", 80); P([(1410, 140), (1450, 140)])
    dot(1450, 140); label(1470, 140, "V_BCKP", "loc"); P([(1450, 140), (1470, 140)])
    cap_v(1450, 140, "C403", "100 nF", 40, "l"); gnd(1450, 180)
    tp(1000, 250, "TP401"); label(1050, 250, "SAFEBOOT", "loc")
    notes(920, 300, ["R402/R403 1 kΩ: Ebyte pide resistencias de protección en la UART; además limitan la",
                     "corriente que entra por RXD con el GNSS apagado (el firmware deja TX en baja/entrada).",
                     "R401: V_BCKP «también puede cargar una pila» ⇒ 1 kΩ limita cualquier conflicto (15 µA ⇒ 15 mV)."])

    # ---------------------------------------------------------------- C · antena
    frame(900, 420, 800, 266, "C · Antena 1575 MHz por U.FL — activa o pasiva")
    ej, _ = ic2(940, 500, 110, "J401", "BWU.FL-IPEX1", [], [("1", "SIG"), ("2", "GND"), ("3", "GND")], pitch=24)
    for k in ("2", "3"):
        x, y = ej[k]; P([(x, y), (x + 10, y)]); gnd(x + 10, y)
    x0, y0 = ej["1"]
    P([(x0, y0), (1180, y0)], "rf"); dot(1180, y0)
    cap_h(1180, y0, "C404", "56 pF C0G", 90); P([(1270, y0), (1330, y0)], "rf"); label(1330, y0, "GNSS_RFIN", "loc")
    P([(1180, y0), (1180, y0 + 20)])
    add(f'<g opacity="0.75">'); ind_v(1180, y0 + 20, "L401", "82 nH (sólo activa)", 60); add('</g>')
    label(1180, y0 + 100, "VCC_RF", "loc", "middle")
    notes(920, 656, ["Pasiva: sólo C404 (DC block). Activa: montar L401 ⇒ la antena recibe VCC_RF (= V_GNSS, 3,3 V)",
                     "por el coaxial; el módulo detecta y protege la antena activa. 50 Ω en coplanar, corto."])

    # ---------------------------------------------------------------- D · alimentación
    frame(20, 700, 860, 250, "D · Alimentación del GNSS")
    caps_to_gnd(120, 760, "V_GNSS", "pwr", [("C401", "10 µF"), ("C402", "100 nF")], dx=90)
    label(500, 760, "3V3", "pwr", "end"); res_h(500, 760, "R404", "0 Ω DNP", 80, sym="dnp"); label(580, 760, "V_GNSS", "pwr")
    notes(40, 860, ["Rizado < 50 mV (§5): V_GNSS sale de su propio buck, separado de los picos de TX del E22.",
                    "R404 sin montar: rectificación si BUCK1 diera guerra (GNSS siempre encendido desde 3V3).",
                    ("🚨 Con R404 montada, BUCK1 debe quedar APAGADO (dos fuentes unidas).", "tw")], dy=19)

    rows = [("U401", "GNSS multibanda", "Ebyte E108-GN04S", "SMD 12,2×16", "—", "cajón #196 (4)"),
            ("J401", "conector antena", "BWU.FL-IPEX1", "SMD", "C5137195", "cajón #210"),
            ("C404", "56 pF C0G", "Samsung CL05C560JB5NNNC", "0402", "C84707", "COMPRAR"),
            ("L401", "82 nH (activa)", "Murata LQG15HS82NJ02D", "0402", "C98002", "COMPRAR"),
            ("R401-R403", "1 kΩ 1 %", "UNI-ROYAL 0402WGF1001TCE", "0402", "C11702", "cajón #31"),
            ("R404", "0 Ω (DNP)", "—", "0402", "—", "—"),
            ("C401", "10 µF 10 V X7R", "—", "0603", "—", "cajón #147"),
            ("C402 C403", "100 nF 16 V X7R", "Samsung CL05B104KO5NNNC", "0402", "C1525", "cajón #22"),
            ("TP401", "punto de prueba", "TestPoint_Pad_D1.0mm", "Ø1 mm", "—", "—")]
    frame(900, 700, 800, 290, "Piezas de la hoja")
    tabla(900, 740, 800, [920, 1010, 1140, 1350, 1450, 1540], ["Ref.", "Qué es", "Pieza", "Encaps.", "LCSC", "Stock"],
          rows, dy=24, mono=(0, 4))
    guardar(OUT)


if __name__ == "__main__":
    dibujar()
